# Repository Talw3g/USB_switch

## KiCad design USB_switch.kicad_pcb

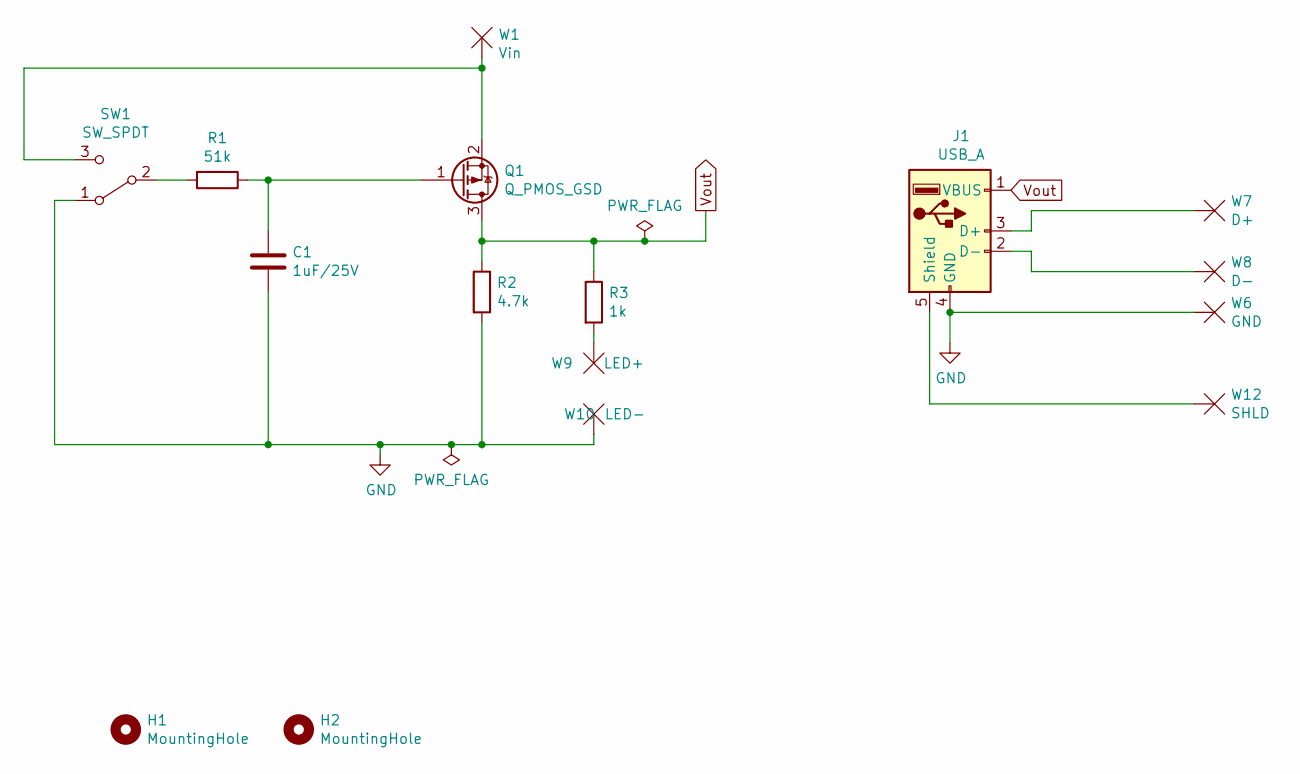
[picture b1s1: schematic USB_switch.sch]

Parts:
C1: 1uF/25V; C_0805_2012Metric_Pad1.15x1.40mm_HandSolder
H1, H2: MountingHole; MountingHole_2.7mm_M2.5_Pad
J1: USB_A; USB_A_Receptacle_Horizontal; Farnell 1642033
Q1: Q_PMOS_GSD; SOT-23; Farnell 1858616
R1: 51k; R_0603_1608Metric_Pad1.05x0.95mm_HandSolder
R2: 4.7k; R_0603_1608Metric_Pad1.05x0.95mm_HandSolder
R3: 1k; R_0603_1608Metric_Pad1.05x0.95mm_HandSolder
SW1: SW_SPDT; Multicomp_Toggle_switch_1MS1T1B5M1QE; Farnell 9473378
W1: Vin; wirepad_hole_2.2x1mm
W6: GND; wirepad_hole_2.2x1mm
W7: D+; wirepad_hole_2.2x1mm
W8: D-; wirepad_hole_2.2x1mm
W9: LED+; wirepad_hole_2.2x1mm
W10: LED-; wirepad_hole_2.2x1mm
W12: SHLD; wirepad_SMD_2.2x4mm

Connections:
GND: C1.2, J1.4 (GND), R2.2, SW1.1 (A), W6.1, W10.1
unnamed: C1.1, Q1.1 (G), R1.1
unnamed: J1.2 (D-), W8.1
unnamed: J1.3 (D+), W7.1
unnamed: J1.5 (Shield), W12.1
unnamed: Q1.2 (S), SW1.3 (C), W1.1
unnamed: R1.2, SW1.2 (B)
unnamed: R3.2, W9.1
Vout: J1.1 (VBUS), Q1.3 (D), R2.1, R3.1

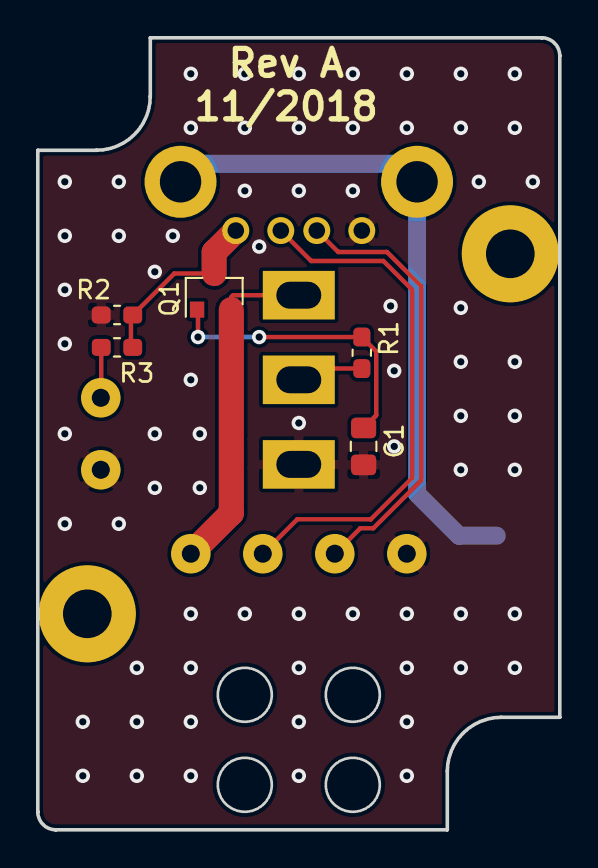
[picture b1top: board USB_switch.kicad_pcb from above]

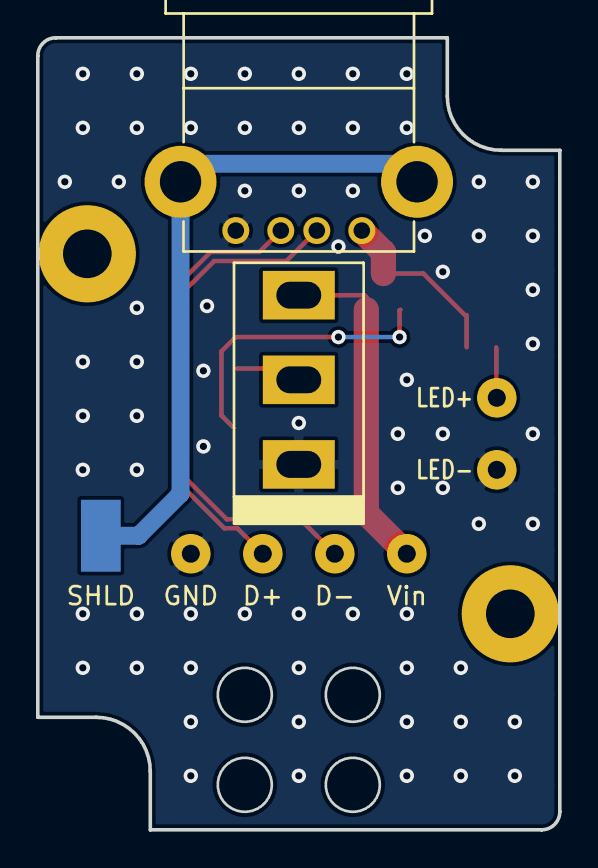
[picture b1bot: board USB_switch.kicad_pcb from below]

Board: 2 copper layers, 29.0 x 44.0 mm, 16 parts (9 on the bottom side), 9 nets.

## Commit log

2018-11-05 Initial commit: schematic and routing done.
2018-11-07 Modified gitignore.
2018-11-07 Added CAD files (WIP).
2018-11-07 Routing done with USB connector.
2018-11-07 CAD model complete.
2018-11-07 Added gerber files.
2018-11-09 Added Rev on silkscreen.
2018-11-13 Updated gitignore
